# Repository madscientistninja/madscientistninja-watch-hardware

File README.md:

# madscientistninja-watch-hardware

See individual components for more details.

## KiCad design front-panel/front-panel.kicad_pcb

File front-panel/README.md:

The contents of this is a front panel
for a watch I am designing it currently
has a wiring issue that shorts all the
buttons because of a misunderstanding of
the pinout, but will be fixed soon.

Custom button footprint is in library folder.
Digikey library is also likely needed.

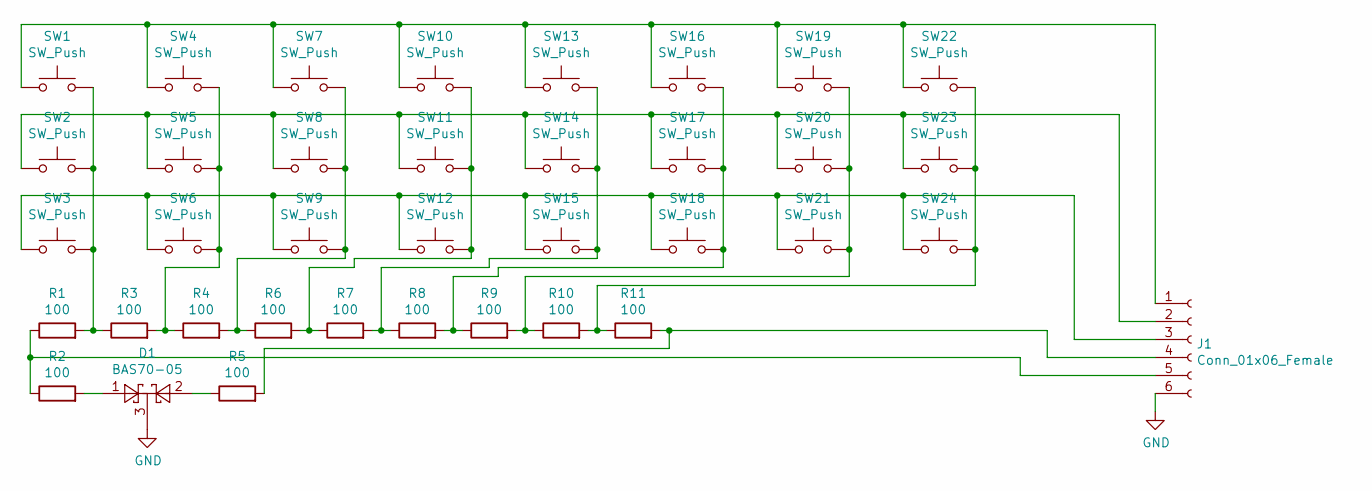
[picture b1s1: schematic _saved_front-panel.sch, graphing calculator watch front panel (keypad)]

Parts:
D1: BAS70-05; SOT-23
J1: Conn_01x06_Female; PinSocket_1x06_P2.54mm_Vertical
R1, R2, R3, R4, R5, R6, R7, R8, R9, R10, R11: 100; R_0402_1005Metric
SW1, SW2, SW3, SW4, SW5, SW6, SW7, SW8, SW9, SW10, SW11, SW12, SW13, SW14, SW15, SW16, SW17, SW18, SW19, SW20, SW21, SW22, SW23, SW24: SW_Push; KMR621NG

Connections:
GND: D1.3, J1.6
unnamed: D1.1, R2.2
unnamed: D1.2, R5.1
unnamed: J1.1, SW1.1, SW4.1, SW7.1, SW10.1, SW13.1, SW16.1, SW19.1, SW22.1
unnamed: J1.2, SW2.1, SW5.1, SW8.1, SW11.1, SW14.1, SW17.1, SW20.1, SW23.1
unnamed: J1.3, SW3.1, SW6.1, SW9.1, SW12.1, SW15.1, SW18.1, SW21.1, SW24.1
unnamed: J1.4, R5.2, R11.2
unnamed: J1.5, R1.1, R2.1
unnamed: R1.2, R3.1, SW1.2, SW2.2, SW3.2
unnamed: R3.2, R4.1, SW4.2, SW5.2, SW6.2
unnamed: R4.2, R6.1, SW7.2, SW8.2, SW9.2
unnamed: R6.2, R7.1, SW10.2, SW11.2, SW12.2
unnamed: R7.2, R8.1, SW13.2, SW14.2, SW15.2
unnamed: R8.2, R9.1, SW16.2, SW17.2, SW18.2
unnamed: R9.2, R10.1, SW19.2, SW20.2, SW21.2
unnamed: R10.2, R11.1, SW22.2, SW23.2, SW24.2

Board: 2 copper layers, 37 parts (0 on the bottom side), 16 nets, no tracks yet.

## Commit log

2019-07-16 Changes to be committed: new file: front-panel/KMRR621NG.kicad_mod new file: front-panel/README.md new file: front-panel/_saved_front-panel.sch new file: front-panel/fp-info-cache new file: front-pan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

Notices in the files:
front-panel/_saved_front-panel.sch:
All Rights Reserved
